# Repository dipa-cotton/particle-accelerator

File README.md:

# particle-accelerator
this is my lil mini particle accelerator that i am making for fun and big joys!!

the pcb is a ring, that will fit around another ring where all the marbles go zoom!!!

## you need:
- (3 leds
- 8 resistors (including one variable and one photo resistor)
- 1 mosfet
- 1 toroid inductor
- 1 12V relay) -> all of this x how many rings you want!
- 1 dc jack connector
- wire to connect everything :)

## why'd i make this?
for sillies! i've really wanted a particle accelerator in my house :)

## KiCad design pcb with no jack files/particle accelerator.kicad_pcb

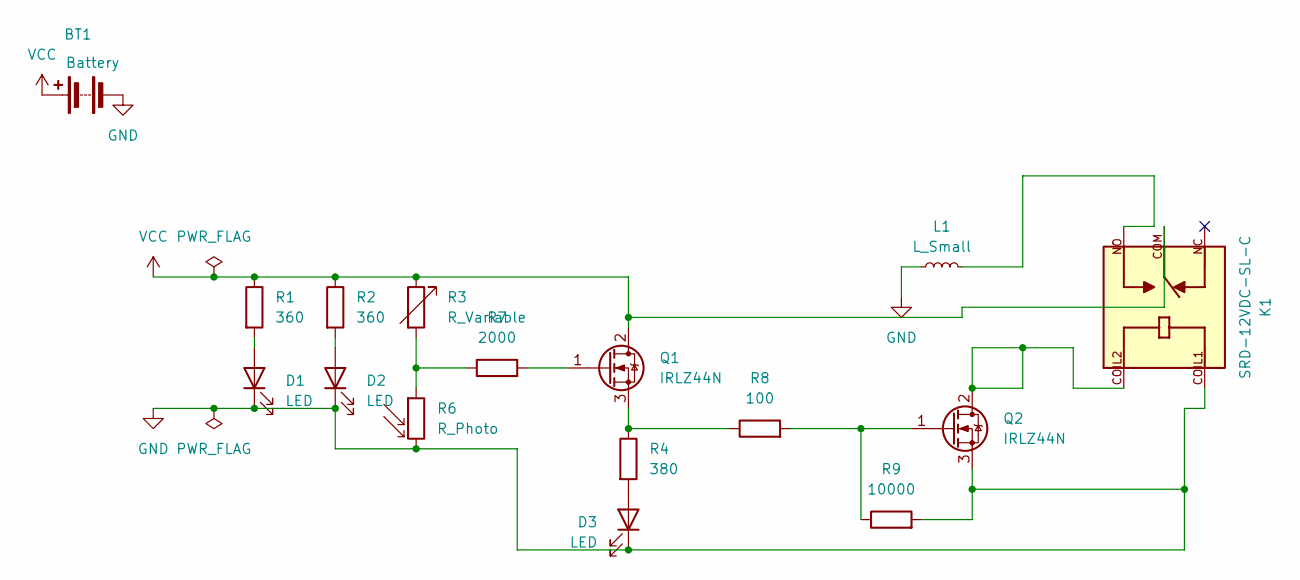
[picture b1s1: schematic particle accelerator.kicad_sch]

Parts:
BT1: Battery; Osram_SFH225
D1, D2, D3: LED; LED_D3.0mm
K1: SRD-12VDC-SL-C; RELAY_SRD-12VDC-SL-C; PARTREV 1.0
L1: L_Small; L_Toroid_Horizontal_D69.1mm_P63.20mm_Vishay_TJ9
Q1, Q2: IRLZ44N; TO-220-3_Vertical
R1, R2: 360; R_Axial_DIN0204_L3.6mm_D1.6mm_P7.62mm_Horizontal
R3: R_Variable; Potentiometer_Bourns_3386W_Horizontal
R4: 380; R_Axial_DIN0204_L3.6mm_D1.6mm_P7.62mm_Horizontal
R6: R_Photo; R_Axial_DIN0204_L3.6mm_D1.6mm_P7.62mm_Horizontal
R7: 2000; R_Axial_DIN0204_L3.6mm_D1.6mm_P7.62mm_Horizontal
R8: 100; R_Axial_DIN0204_L3.6mm_D1.6mm_P7.62mm_Horizontal
R9: 10000; R_Axial_DIN0204_L3.6mm_D1.6mm_P7.62mm_Horizontal

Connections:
GND: BT1.2 (-), D1.1 (K), D2.1 (K), D3.1 (K), K1.COIL1, L1.1, Q2.3 (S), R6.2, R9.2
unnamed: D1.2 (A), R1.2
unnamed: D2.2 (A), R2.2
unnamed: D3.2 (A), R4.2
unnamed: K1.NO, L1.2
unnamed: Q1.1 (G), R7.2
unnamed: Q1.3 (S), R4.1, R8.1
unnamed: K1.COIL2, Q2.2 (D)
unnamed: Q2.1 (G), R8.2, R9.1
unnamed: R3.2, R6.1, R7.1
VCC: BT1.1 (+), K1.COM, Q1.2 (D), R1.1, R2.1, R3.1

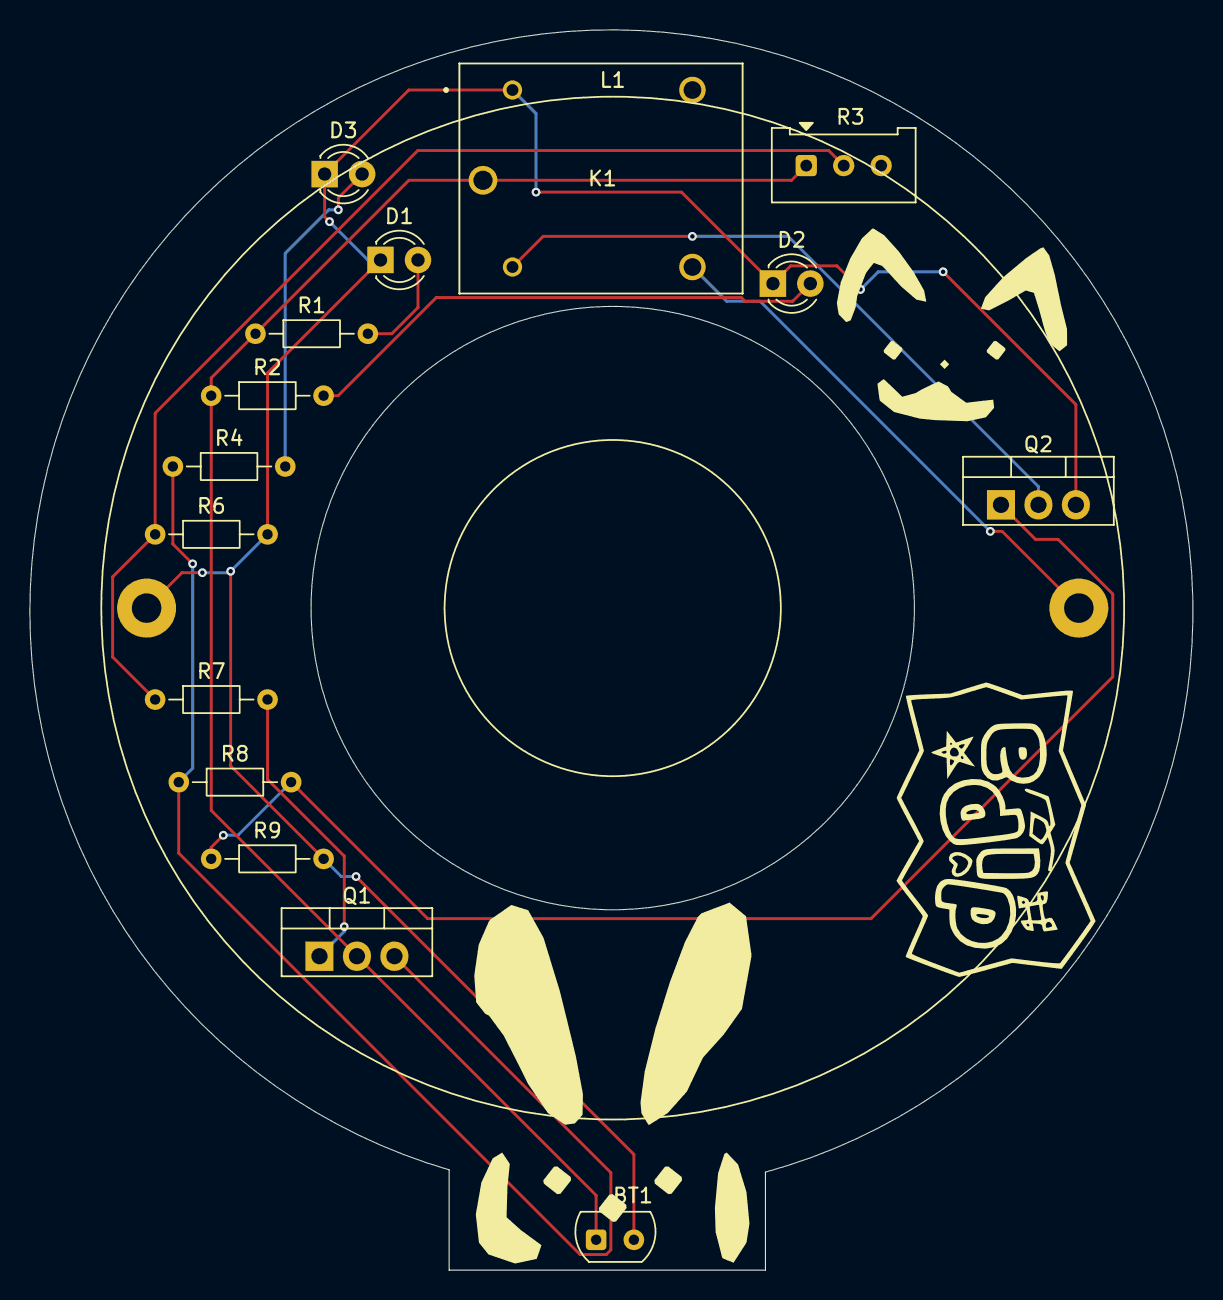
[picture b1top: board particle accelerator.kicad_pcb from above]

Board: 2 copper layers, 78.8 x 84.1 mm, 16 parts (0 on the bottom side), 11 nets.

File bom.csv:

'Reference'|'Qty'|'Value'|'DNP'|'Exclude from BOM'|'Exclude from Board'|'Footprint'|'Datasheet'
'BT1'|'1'|'Battery'|''|''|''|'OptoDevice:Osram_SFH225'|''
'D1,D2,D3'|'3'|'LED'|''|''|''|'LED_THT:LED_D3.0mm'|''
'J1'|'1'|'Barrel_Jack_Switch'|''|''|''|'Connector_BarrelJack:BarrelJack_Horizontal'|''
'K1'|'1'|'SRD-12VDC-SL-C'|''|''|''|'Relay:RELAY_SRD-12VDC-SL-C'|''
'L1'|'1'|'L_Small'|''|''|''|'Inductor_THT:L_Toroid_Horizontal_D69.1mm_P63.20mm_Vishay_TJ9'|''
'Q1,Q2'|'2'|'IRLZ44N'|''|''|''|'Package_TO_SOT_THT:TO-220-3_Vertical'|'http://www.irf.com/product-info/datasheets/data/irlz44n.pdf'
'R1,R2'|'2'|'360'|''|''|''|'Resistor_THT:R_Axial_DIN0204_L3.6mm_D1.6mm_P7.62mm_Horizontal'|''
'R3'|'1'|'R_Variable'|''|''|''|'Potentiometer_THT:Potentiometer_Bourns_3386W_Horizontal'|''
'R4'|'1'|'380'|''|''|''|'Resistor_THT:R_Axial_DIN0204_L3.6mm_D1.6mm_P7.62mm_Horizontal'|''
'R6'|'1'|'R_Photo'|''|''|''|'Resistor_THT:R_Axial_DIN0204_L3.6mm_D1.6mm_P7.62mm_Horizontal'|''
'R7'|'1'|'2000'|''|''|''|'Resistor_THT:R_Axial_DIN0204_L3.6mm_D1.6mm_P7.62mm_Horizontal'|''
'R8'|'1'|'100'|''|''|''|'Resistor_THT:R_Axial_DIN0204_L3.6mm_D1.6mm_P7.62mm_Horizontal'|''
'R9'|'1'|'10000'|''|''|''|'Resistor_THT:R_Axial_DIN0204_L3.6mm_D1.6mm_P7.62mm_Horizontal'|''
